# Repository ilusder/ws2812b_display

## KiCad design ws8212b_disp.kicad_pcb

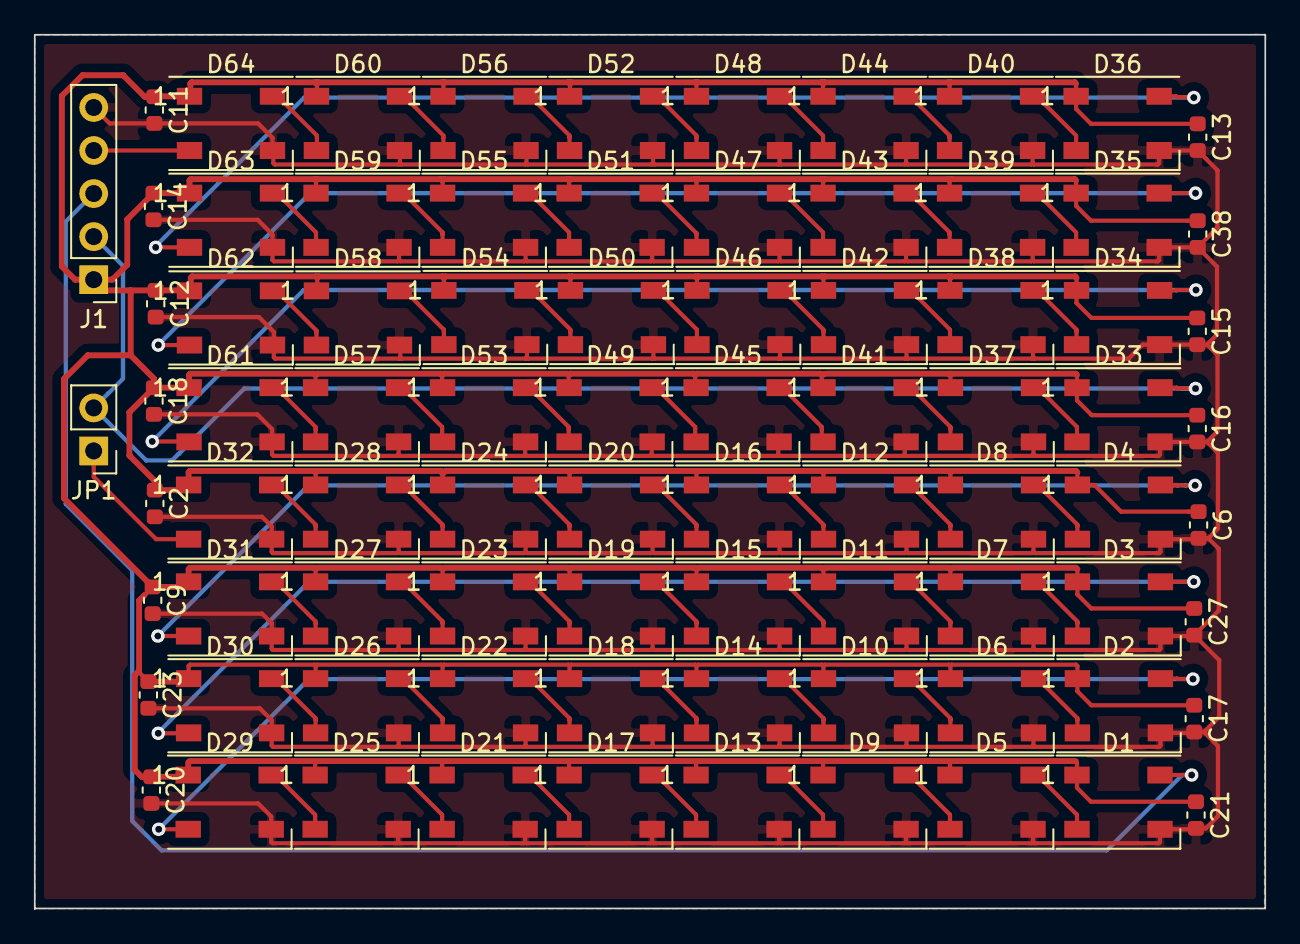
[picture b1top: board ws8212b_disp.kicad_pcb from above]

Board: 2 copper layers, 72.6 x 51.6 mm, 82 parts (0 on the bottom side), 68 nets.

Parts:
C2, C6, C9, C11, C12, C13, C14, C15, C16, C17, C18, C20, C21, C23, C27, C38: 100n; C_0603_1608Metric
D1, D2, D3, D4, D5, D6, D7, D8, D9, D10, D11, D12, D13, D14, D15, D16, D17, D18, D19, D20, D21, D22, D23, D24, D25, D26, D27, D28, D29, D30, D31, D32, D33, D34, D35, D36, D37, D38, D39, D40, D41, D42, D43, D44, D45, D46, D47, D48, D49, D50, D51, D52, D53, D54, D55, D56, D57, D58, D59, D60, D61, D62, D63, D64: WS2812B; LED_WS2812B_PLCC4_5.0x5.0mm_P3.2mm
J1: IN; PinHeader_1x05_P2.54mm_Vertical
JP1: S/P; PinHeader_1x02_P2.54mm_Vertical

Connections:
/DIN1: D1.4, J1.3
/DIN2: D33.4, J1.2, JP1.2
/DOUT: D64.2, J1.4
/Sheet5F97A0BD/DOUT: D32.2, JP1.1
/VDD: C2.1, C6.1, C9.1, C11.1, C12.1, C13.1, C14.1, C15.1, C16.1, C17.1, C18.1, C20.1, C21.1, C23.1, C27.1, C38.1, D1.1, D2.1, D3.1, D4.1, D5.1, D6.1, D7.1, D8.1, D9.1, D10.1, D11.1, D12.1, D13.1, D14.1, D15.1, D16.1, D17.1, D18.1, D19.1, D20.1, D21.1, D22.1, D23.1, D24.1, D25.1, D26.1, D27.1, D28.1, D29.1, D30.1, D31.1, D32.1, D33.1, D34.1, D35.1, D36.1, D37.1, D38.1, D39.1, D40.1, D41.1, D42.1, D43.1, D44.1, D45.1, D46.1, D47.1, D48.1, D49.1, D50.1, D51.1, D52.1, D53.1, D54.1, D55.1, D56.1, D57.1, D58.1, D59.1, D60.1, D61.1, D62.1, D63.1, D64.1, J1.1
GND: C2.2, C6.2, C9.2, C11.2, C12.2, C13.2, C14.2, C15.2, C16.2, C17.2, C18.2, C20.2, C21.2, C23.2, C27.2, C38.2, D1.3, D2.3, D3.3, D4.3, D5.3, D6.3, D7.3, D8.3, D9.3, D10.3, D11.3, D12.3, D13.3, D14.3, D15.3, D16.3, D17.3, D18.3, D19.3, D20.3, D21.3, D22.3, D23.3, D24.3, D25.3, D26.3, D27.3, D28.3, D29.3, D30.3, D31.3, D32.3, D33.3, D34.3, D35.3, D36.3, D37.3, D38.3, D39.3, D40.3, D41.3, D42.3, D43.3, D44.3, D45.3, D46.3, D47.3, D48.3, D49.3, D50.3, D51.3, D52.3, D53.3, D54.3, D55.3, D56.3, D57.3, D58.3, D59.3, D60.3, D61.3, D62.3, D63.3, D64.3, J1.5
unnamed: D1.2, D5.4
unnamed: D2.2, D6.4
unnamed: D2.4, D29.2
unnamed: D3.2, D7.4
unnamed: D3.4, D30.2
unnamed: D4.2, D8.4
unnamed: D5.2, D9.4
unnamed: D10.2, D14.4
unnamed: D6.2, D10.4
unnamed: D11.2, D15.4
unnamed: D7.2, D11.4
unnamed: D12.2, D16.4
unnamed: D8.2, D12.4
unnamed: D13.2, D17.4
unnamed: D9.2, D13.4
unnamed: D14.2, D18.4
unnamed: D15.2, D19.4
unnamed: D16.2, D20.4
unnamed: D17.2, D21.4
unnamed: D18.2, D22.4
unnamed: D19.2, D23.4
unnamed: D20.2, D24.4
unnamed: D21.2, D25.4
unnamed: D22.2, D26.4
unnamed: D23.2, D27.4
unnamed: D24.2, D28.4
unnamed: D25.2, D29.4
unnamed: D26.2, D30.4
unnamed: D27.2, D31.4
unnamed: D28.2, D32.4
unnamed: D4.4, D31.2
unnamed: D33.2, D37.4
unnamed: D34.2, D38.4
unnamed: D34.4, D61.2
unnamed: D35.2, D39.4
unnamed: D35.4, D62.2
unnamed: D36.2, D40.4
unnamed: D36.4, D63.2
unnamed: D37.2, D41.4
unnamed: D38.2, D42.4
unnamed: D39.2, D43.4
unnamed: D40.2, D44.4
unnamed: D41.2, D45.4
unnamed: D42.2, D46.4
unnamed: D43.2, D47.4
unnamed: D44.2, D48.4
unnamed: D45.2, D49.4
unnamed: D46.2, D50.4
unnamed: D47.2, D51.4
unnamed: D48.2, D52.4
unnamed: D49.2, D53.4
unnamed: D50.2, D54.4
unnamed: D51.2, D55.4
unnamed: D52.2, D56.4
unnamed: D53.2, D57.4
unnamed: D54.2, D58.4
unnamed: D55.2, D59.4
unnamed: D56.2, D60.4
unnamed: D57.2, D61.4
unnamed: D58.2, D62.4
unnamed: D59.2, D63.4
unnamed: D60.2, D64.4

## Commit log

2020-09-22 Init project
